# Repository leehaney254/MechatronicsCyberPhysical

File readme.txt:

Brief project description:
This project aims to monitor the operation carried out in a mechatronic system station. 
The device controls access to a Mechatronic station and also monitors the processes happening in the system, 
in real time.

Rule:
Always push a working code, design, and analysis with their documentation.

version:
1.1.1 alpha

Communication with matalab
When communicating  with matlab its hard to debug if the information had been recieved
by the microcontroller. However, teensy has mutliple virtual communication ports where one 
can be used to communicate with the pc application(matlab) and the others can be used in 
debugging. This process is made smoother by tytools( https://github.com/Koromix/tytools )

web
We use ajax to constantly update our webpage without refreshing
we use ejs for templating

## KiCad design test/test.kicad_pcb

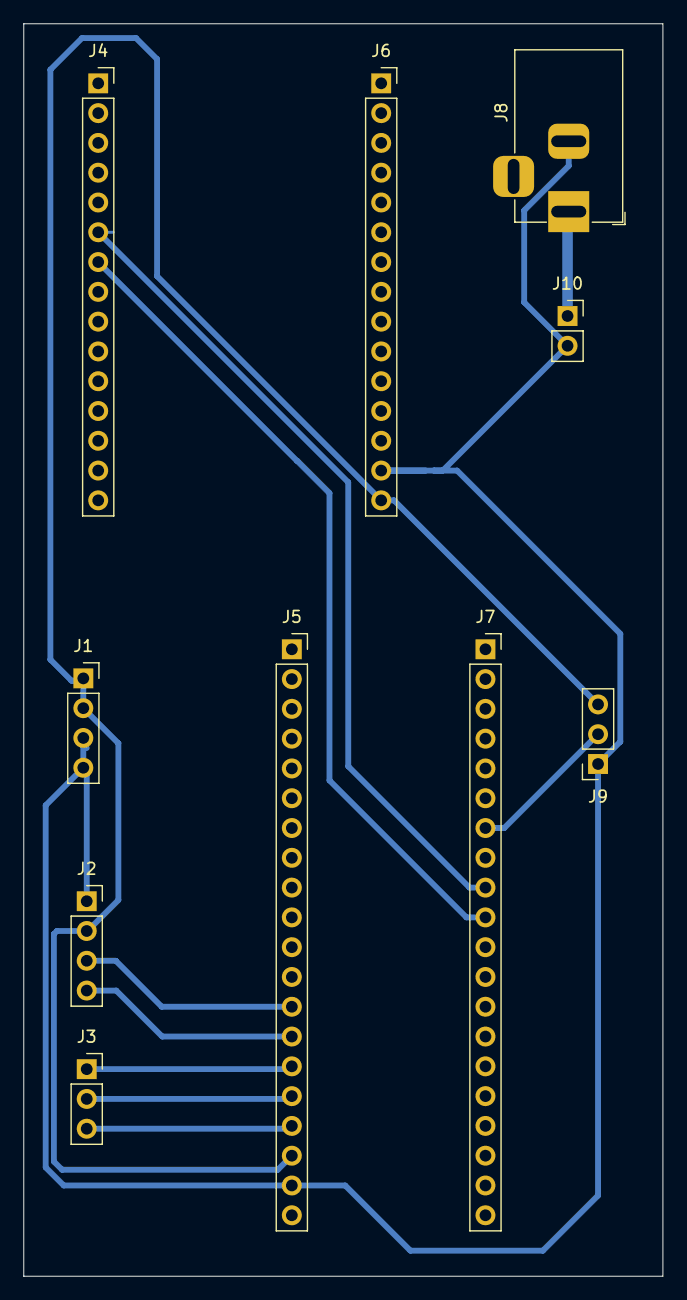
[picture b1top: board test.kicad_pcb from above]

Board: 2 copper layers, 54.5 x 106.8 mm, 10 parts (0 on the bottom side), 11 nets.

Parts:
J1: POWER; PinSocket_1x04_P2.54mm_Vertical
J2: ENCODER; PinSocket_1x04_P2.54mm_Vertical
J3: Motor_driver; PinSocket_1x03_P2.54mm_Vertical
J4: Left_esp32; PinSocket_1x15_P2.54mm_Vertical
J5: left_stm32; PinSocket_1x20_P2.54mm_Vertical
J6: Right_esp32; PinSocket_1x15_P2.54mm_Vertical
J7: right_stm32; PinSocket_1x20_P2.54mm_Vertical
J8: Barrel_Jack; BarrelJack_Horizontal
J9: current_sensor; PinSocket_1x03_P2.54mm_Vertical
J10: 12V_SOURCE; PinSocket_1x02_P2.54mm_Vertical

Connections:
/5V: J1.1, J1.2, J2.2, J5.18, J6.15, J9.3
/12V: J8.1, J10.1
/A0: J7.7, J9.2
/A2: J4.6, J7.9
/A3: J4.7, J7.10
/ENA: J2.3, J5.13
/ENAB: J3.1, J5.15
/ENB: J2.4, J5.14
/GND: J1.3, J1.4, J2.1, J5.19, J6.14, J8.2, J9.1, J10.2
/IN1: J3.2, J5.16
/IN2: J3.3, J5.17

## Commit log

2022-03-09 readme push
2022-03-23 new changes
2022-03-26 NewAddings
2022-03-31 Kicad circuit
2022-04-14 adding to proteaus
2022-04-14 model design upload
2022-04-19 my testing
2022-06-22 Our website side bar
2022-06-22 changes to nav bar
2022-06-22 adding different pages
2022-06-24 adding matlab link
2022-06-24 communicating with matlab
2022-06-25 More changes on views
2022-06-26 Achieved communication with firebase
2022-06-29 Teensy communicating with matlab using tytools
2022-07-07 work improvement
2022-07-12 adding express
2022-07-12 sending json data esp32
2022-07-12 views with static files together
2022-07-12 changing database
2022-07-12 Bringing the data to front end
2022-07-12 Deleted unecessary files
2022-07-13 tests
2022-07-13 testing polling of data
2022-07-13 sending real time data
2022-07-27 trying threejs
2022-09-02 txt changes
2022-09-21 working embedded
2022-09-21 new db
2022-09-22 site with matlab
2022-09-22 working codes
2022-09-22 working website
